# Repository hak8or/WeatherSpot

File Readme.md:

## WeatherSpot

A weather reporting ecosystem consisting of a website, windows native application, and multiple weather sensors to fetch weather data.

### Development
1. Login to the WeatherSpot server using ```ssh root@WeatherSpot.us```.
2. Make sure the influx database is running using ```docker ps -a``` to see active containers. If it's not running, a ```docker start weather_db``` will get it up again.
3. Do whatever you need to do.

In the event the influxdb container was removed, the following will get it up again:
```bash
docker run -d -p 8083:8083 -p 8084:8084 -p 8086:8086 -e PRE_CREATE_DB="weather" --name weather_db tutum/influxdb:latest
```

### Docker Installation
```bash
# Have to use this script since the official repo has an outdated (v1.5) docker.
wget -qO- https://get.docker.com/ | sh

# Unmasks the services.
systemctl unmask docker.service
systemctl unmask docker.socket

# And starts them.
systemctl start docker.service
systemctl start docker.socket
```

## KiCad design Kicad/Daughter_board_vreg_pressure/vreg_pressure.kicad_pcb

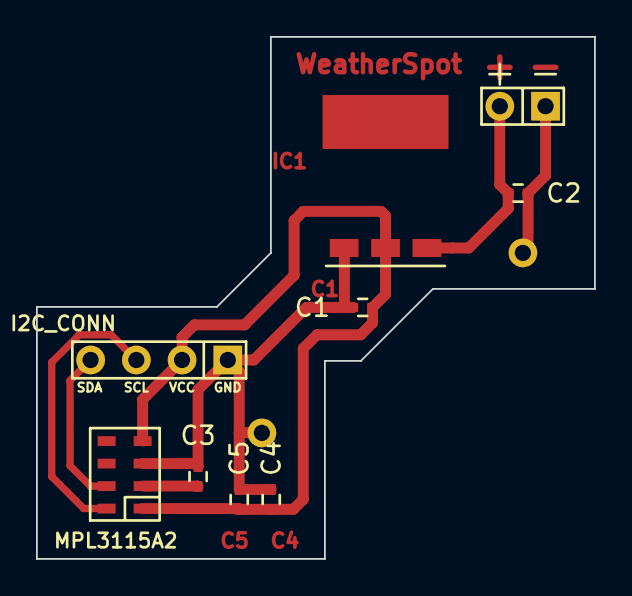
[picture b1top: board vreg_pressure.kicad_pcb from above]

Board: 2 copper layers, 31.0 x 29.0 mm, 11 parts (0 on the bottom side), 6 nets.

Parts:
C1, C4: 10uF; C_0402
C2: 2.2uF; C_0402
C3, C5: 0.1uF; C_0402
IC1: SPX1117M3
J1: BATT; BATT_CONN
U1: MPL3115A2
VIA_HOME_ETCH: VAL**; VIA_HOME_ETCH
VIA_HOME_ETCH#2: VAL**; VIA_HOME_ETCH
conn1: I2C_CONN

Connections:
3V3: C1.1, C4.1, C5.1, IC1.2, U1.1, U1.4, conn1.3
GND: C1.2, C2.2, C3.2, C4.2, C5.2, IC1.1, J1.1, U1.3, VIA_HOME_ETCH.1, VIA_HOME_ETCH#2.1, conn1.4
unnamed: C2.1, IC1.3, J1.2
unnamed: C3.1, U1.2
unnamed: U1.7, conn1.1
unnamed: U1.8, conn1.2

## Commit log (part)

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2015-06-06 Added rough readme
2015-06-07 Fixed docker run to docker start for db
2015-06-07 Components List. This will expand as the schematics are made.
2015-06-07 Initialization of the kicad project
2015-06-07 Set the appropriate title, description and comments.
2015-06-07 finished the initial atmega328p circuit
2015-06-07 added more components to the list
2015-06-07 added a voltage regulator circuit
2015-06-07 added a photoresitor circuit
2015-06-07 added temperature/humidity circuit
2015-06-08 final schematic clean up
2015-06-08 PDF file for easier schematic viewing
2015-06-10 Added proper port for HTTP access to influxdb to readme
2015-06-10 initial HTML files
2015-06-15 added wifi module
2015-06-15 Cleaned up and added Test points in various locations for probing
2015-06-15 added extra connections for SPI and I2C
2015-06-15 updated the PDF to reflect the latest schematic changes
2015-06-15 updated project file
2015-06-15 annotated components
2015-06-15 updated PDF with annotations of components
2015-06-16 netlist of components
2015-06-16 custom schematics components
2015-06-17 Beginning of backend components for interacting with database, index.html for querying our database and query.php for running queries on the server side
2015-06-17 PHP wrapper for querying InfluxDB, index.html for reporting queries from the wrapper
2015-06-18 Renamed project folder to something more descriptive
2015-06-18 Added rough DHT11 support
2015-06-18 Added teensy support for heartbeat GPIO.
2015-06-18 Added stop functionality for heartbeat timer.
2015-06-18 Create linegraph
2015-06-19 Optimized report table, greatly reduced the number of append() calls
2015-06-19 More fixes of index.html, first commit of data visualization with d3.js
2015-06-20 switched website to bootstrap
2015-06-23 delme fw quickie
2015-06-25 Queries are now done by a database user with read permission only, no more dropping and deleting
2015-06-25 Added support for user creditials to be passed to query wrapper
2015-06-25 Code cleanup
2015-06-29 Create locations.html
    Map of Locations of our WeatherStations
2015-07-01 Extended wrapper to work for writing data, now POST data to the wrapper with the "data" parameter, an example is included on line 21. The data posted under the data parameter should be of the followi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
2015-07-01 windows app initial files
2015-07-01 Update locations.html
    Has two locations plus clicking them will bring up info menu
2015-07-02 Added explorer.html for example of using ajax and displaying query results
2015-07-03 implemented import routine, reorganized code, added PlottingClass.cs
2015-07-03 implemented export routine, fixed out of bounds issue in PlottingClass.cs
2015-07-04 implemented rough statistics section
2015-07-04 added console implementation, reorganized code, added NetworkClass.cs
2015-07-05 created proper about section
2015-07-07 Posting to thingspeak as an example now works.
2015-07-07 Made it easier to structure data for submitting to the database, now instead of taking parameters from the body of the POST request the parameters are instead pulled from the URL. To write a point to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
2015-07-09 Psh, who needs proper commit messeges?
2015-07-14 Make the git "Website" folder actually reflect what our website is running.
2015-07-14 Mismanaged git problems?
2015-07-14 Added better find function for serial comms
2015-07-14 improved stability, added exception handlers
2015-07-15 added console history
2015-07-19 added day selection for the data graph
2015-07-19 Added light reading sensor
2015-07-20 Added better configuration for wifi connectivity
2015-07-20 Changed pins for WIFI module serial comms to board pins
2015-07-20 Fixed find function and cleaned up commands for new ESP firmware.
2015-07-20 Fixed wifi IP address dump info
2015-07-20 Added ping test to our server
2015-07-20 Updated AP connection command to non depricated version
2015-07-20 Went back to using a single TCP connection instead of allowing multiple
2015-07-20 Cleaned up sending packets to backend
2015-07-20 Implimented heartbeat panic if connectivity goes wrong
2015-07-20 Removed now useless ethercard lib zip
2015-07-20 Added a gitignore, specifically for sublime text
2015-07-20 Added check for if DHT module is not init correctly
2015-07-20 Cleaned up includes in main .ino file
2015-07-20 Fixed DHT11 module not working earlier
2015-07-21 final components routing for version 0.2
2015-07-21 updated components
2015-07-21 final schematics and net list
2015-07-21 zipped gerber files of the v0.2 boards
2015-07-21 removed repetitive/never-active code
2015-07-21 moved the loop to its native spot since we never need to break out of it
2015-07-21 moved the object initializers to a global scope - its an embedded system, its ok :P
2015-07-21 added timerone.h library to the main folder - this way we can keep in sync
2015-07-21 fixed the led restart after panic mode
2015-07-26 Added a queryFactory form to d3query.html, this form should make it easier for users to makes graphs using the database, without having to know influxDB's language beforehand. There is much room for 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
2015-07-26 newest PDF for the weather station unit
2015-07-26 Initialized daughter board project
2015-07-26 added new components to the library
2015-07-26 added cap values and annotated the schematics
2015-07-26 added a pdf for the curious
2015-07-26 net list and schematics finalized
2015-07-26 pcb finalized
2015-07-26 components finalized
2015-07-26 Added a "No Data" alert when no data is returned from a query, fixed queryFactory constructor
2015-07-26 Updated constructor to make queryFactory more modular- a queryFactory is now constructed using a selector for an element to append queryFactory to, the text of the "Query Button" for querying, and th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
    Improved default time values when adding a new WHERE clause- upon clicking the "Add Where Clause" button the first two times will now create a query returning the last 24 hours of data.
    Added reset button to reset WHERE Clause textboxes, put a pink outline around the queryFactory area.
2015-07-26 Added a LIMIT Textbox for limitting queries.
2015-07-26 Made it more noticable when a query does not return any data.
2015-07-26 Moved queryFactory into its own object literal in order to minimize clutter in global namespace.
2015-07-27 Fancy refactoring into an anonymous function in order to allow for public/private encapsulation, as recommended by a Javascript best practices blog post. http://appendto.com/2010/10/how-good-c-habits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
2015-07-27 More cleanup
2015-07-28 final uncommitted fixes
2015-07-28 increased the number of graphs to 4, improved statistics, rearranged GUI elements
2015-07-31 Created for the purpose of having a way to include graphs on any page simply
2015-07-31 Added a list bar to the side of the Map, fixed InfoWindows not closing. Added graphs below the Map to display most recent 100 points of data.
2015-08-01 Added minimum height to cause html element to fill Viewport, added section tag styles for centering logo and text below it
2015-08-01 A semicolon
2015-08-01 Added content headers for Viewport width scaling, added content header for HandheldFriendly; attempting to be responsive for all mobile devices. Added "Get Started" link to Google Maps page, centered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
2015-08-01 added support for the pressure sensor
2015-08-01 added light sensor to be pushed to server
2015-08-01 removed hardcoded values
2015-08-01 fixed pinout for the wifi module
2015-08-01 fixed connection issues when connecting to a new network
2015-08-01 removed the while(true) loop
2015-08-01 Made layout more aestetic, balanced left and right sides of the page, removed some margins, set styles on portrait mode so when in portrait mode the map takes up less space and the sidebar list can b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
2015-08-02 Added class with a box shadow to <section> element
2015-08-02 Added a blue box shadow created with http://www.cssmatic.com/box-shadow
2015-08-02 added a time stamp to each loop run
2015-08-02 moved the network joining to the main loop
2015-08-02 if the send fails 3 times, the module will be restarted - prevents infinite loop
2015-08-02 disconnect the wifi module from the AP to conserve energy and delay 2 min
2015-08-03 added sleep mode instead of delay for the atmega
2015-08-03 improved import and export functions which now support 4 graphs
2015-08-04 added the led off code in the proper spot
2015-08-04 Removed unused teensy code for heartbeat
2015-08-04 wake up the light after the measurements have been taken as to not have light pollution
2015-08-04 blink the led in sleep mode every 9 seconds for 1 second
2015-08-04 power saver - such is life
2015-08-04 changed mode
2015-08-04 wall power dependent loop - seems to be super stable
2015-08-04 reconnect if we detect a problem wiht the send - if fails it will try again in 2 min
2015-08-05 Html and Body width/height, body background is now new lightblue circular gradient
2015-08-05 Updated graph Y-axis scaling to be +/- 1% of the range
2015-08-05 Awesome font with clouds
2015-08-05 Removed iFrame element, now display graphs with graphFactory.js
2015-08-05 Functions for making graphs to append to a chosen element
2015-08-05 Renamed to graphFactory.js
2015-08-05 Implemented graphFactory, moved some CSS out to rest.css, added new styles for sidebar list, changed font of sidebar list, changed highlighting colors.
2015-08-05 Logo, cropped but still needs more cropping
2015-08-05 Changed layout while in portrait mode
2015-08-05 Removed inline styling, moved styles into location.css
2015-08-05 Chained removes together to improve performance, fixed 'Reset' button handling
2015-08-06 Moved google maps script into `js/location.js`
2015-08-06 Code from locations.html Google Maps script
2015-08-07 kill the light before taking measurements
2015-08-07 Added rotation to text to display tilted timestamps
2015-08-07 Moved styles from `locations.html` into a css file
2015-08-07 Changed query for graph, changed graph titles, increased number of ticks on x-axis, added styles to text element
2015-08-07 Changed container to insert graphs into, changed click event of markers to scroll down to graph section of page
2015-08-07 Added a new container for graphs, added a line break to fix error in webkit.
2015-08-07 Changed onclick method to auto-scroll down to graphs when they are displayed.
2015-08-07 Wrapped graphs into a container
2015-08-10 Added doxygen comments to setup and loop
2015-08-10 Added define for SSID credentials
2015-08-10 Cleaned up formatting of tabs vs spaces and general code style cleanup
2015-08-10 Cleaned header for weatherspot serial info.
2015-08-10 Removed outdated or redundant comments and CH_PD functionality
2015-08-10 Cleaned up loop startup serial print
2015-08-10 Made function for printing sensor data
2015-08-10 Cleaned up main loop completion section
2015-08-10 Using pragma once for header files
2015-08-10 Added comment as to why wifi setup always returns true
2015-08-10 Removed serial proxy for wifi and added series selection for send_packet()
2015-08-10 Added null set for pressure sensor in Sensors::Sensors()
2015-08-10 Cleaned up formatting for Sensors::read_sensors()
2015-08-10 Added serial print for succesfull data transmission
2015-08-10 Cleaned up print headers for network fails and info
2015-08-10 Added comment for reply_length argument for Network::find
2015-08-10 Added comments for each class
2015-08-10 Moved sensor_data struct into Sensors class
2015-08-10 Removed unused data_pin Sensors data member
2015-08-10 Now using Arduino installed timerone lib instead of direct header
2015-08-10 Cleaned up comments for Network::send_packet()
2015-08-10 Added filters by range for parameters to avoid outliers getting into the database
2015-08-10 Added "Fork Me On Github" banner, hid "Main" link in list
2015-08-10 Moved "Get Started" button
2015-08-10 Cleanup
2015-08-10 Updated download icon
2015-08-10 Changed menu item entry to Windows Application
2015-08-10 Added graphData(data) for graphing cached queries without repeating network request, redraw graphs when window resizes
2015-08-10 Reduced timeout of page scrolling
2015-08-10 Changed menu item to Windows Application
2015-08-11 removed the vreg and left the pressure sensor.
2015-08-11 fixed UNIX timestamp in console section
2015-08-11 Extended startup banner
